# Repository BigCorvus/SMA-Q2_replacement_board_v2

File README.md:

# SMA-Q2_replacement_board_v2

nRF5840-based replacement board for the SMA-Q2 smartwatch. Uses the MDBT50Q-1MV2 (and similar) module. Based on the Adafruit Feather nRF52840. Has to be fabricated on 0,8mm FR4 material. Main changes are: no external RTC, all mosfets in SOT-323 package (at least in v2.2), optional barometer and power latching circuit, everything controlled by the nRF52840.

2 versions have been created: v2.2 without MS5611 barometer, but with a simple power latching circuit. v2.1.1 does not have a power latching circuit, but has a footprint for a MS5611 barometer. Both versions use both interrupts of the accelerometer.  
During testing and everyday use RF performance turned out to be poor. The reason is the ceramic antenna which is shielded by the close proximity of the lipo battery. This problem was quite easy to solve in retrospective. I just desoldered the chip antenna with 2 soldering irons and connected a simple 30AWG wire which I shortened until reception started to get worse. Ended up with about 20mm of wire bent around the top left corner of the device where least interfering metal is located. Quite surprising that the antenna is quite a bit shorter than one would expect for 2.4GHz (lambda/4 = ~31mm). Let me tell you, at 5dbm TX power the wireless range and link reliability is now really good! FCC compliance is now goneski of course.  
This got me motivated to create a 3rd version of the board using the bare chip instead of an integrated module. It makes use of the inbuilt antenna which is also surprisingly short (about 20mm). The feedline was designed to be about 50 ohm (although it probably doesn't have to be, in the original version it's about 65 ohm at 0,7mm trace width and 0.8mm FR4 substrate). This version 2.3 has the barometer, which has proven to be very accurate and useful, the power latching circuit and even a fuel gauge which can measure the supply current (albeit in 1mA steps).  
Another feature that proved to be very useful if you like to wear a dev platform on your wrist is a normally closed reed switch in series with the battery so you can power cycle the device if bricked with a magnet (the charging cable f.e.) or just keep the battey disconnected by attaching a magnet to it if the device is not in use and has to be stored for longer periods of time. The pads on the bottom of the board are there to keep the reed switch in place. The battery therefore connects to the leftmost contact (one arm of the reed switch) and GND. I used the smallest SPDT (3 pins) reed switch I could find. Its glass body is 15mm long. Just trim the unused leg and bend the other two in shape carefully making sure the delicate glass body stays intact.   

Note: 2.3 has not been tested yet. The Feather bootloader should still work, the pinout for the button, I2C, SPI, QSPI and UART is still the same.

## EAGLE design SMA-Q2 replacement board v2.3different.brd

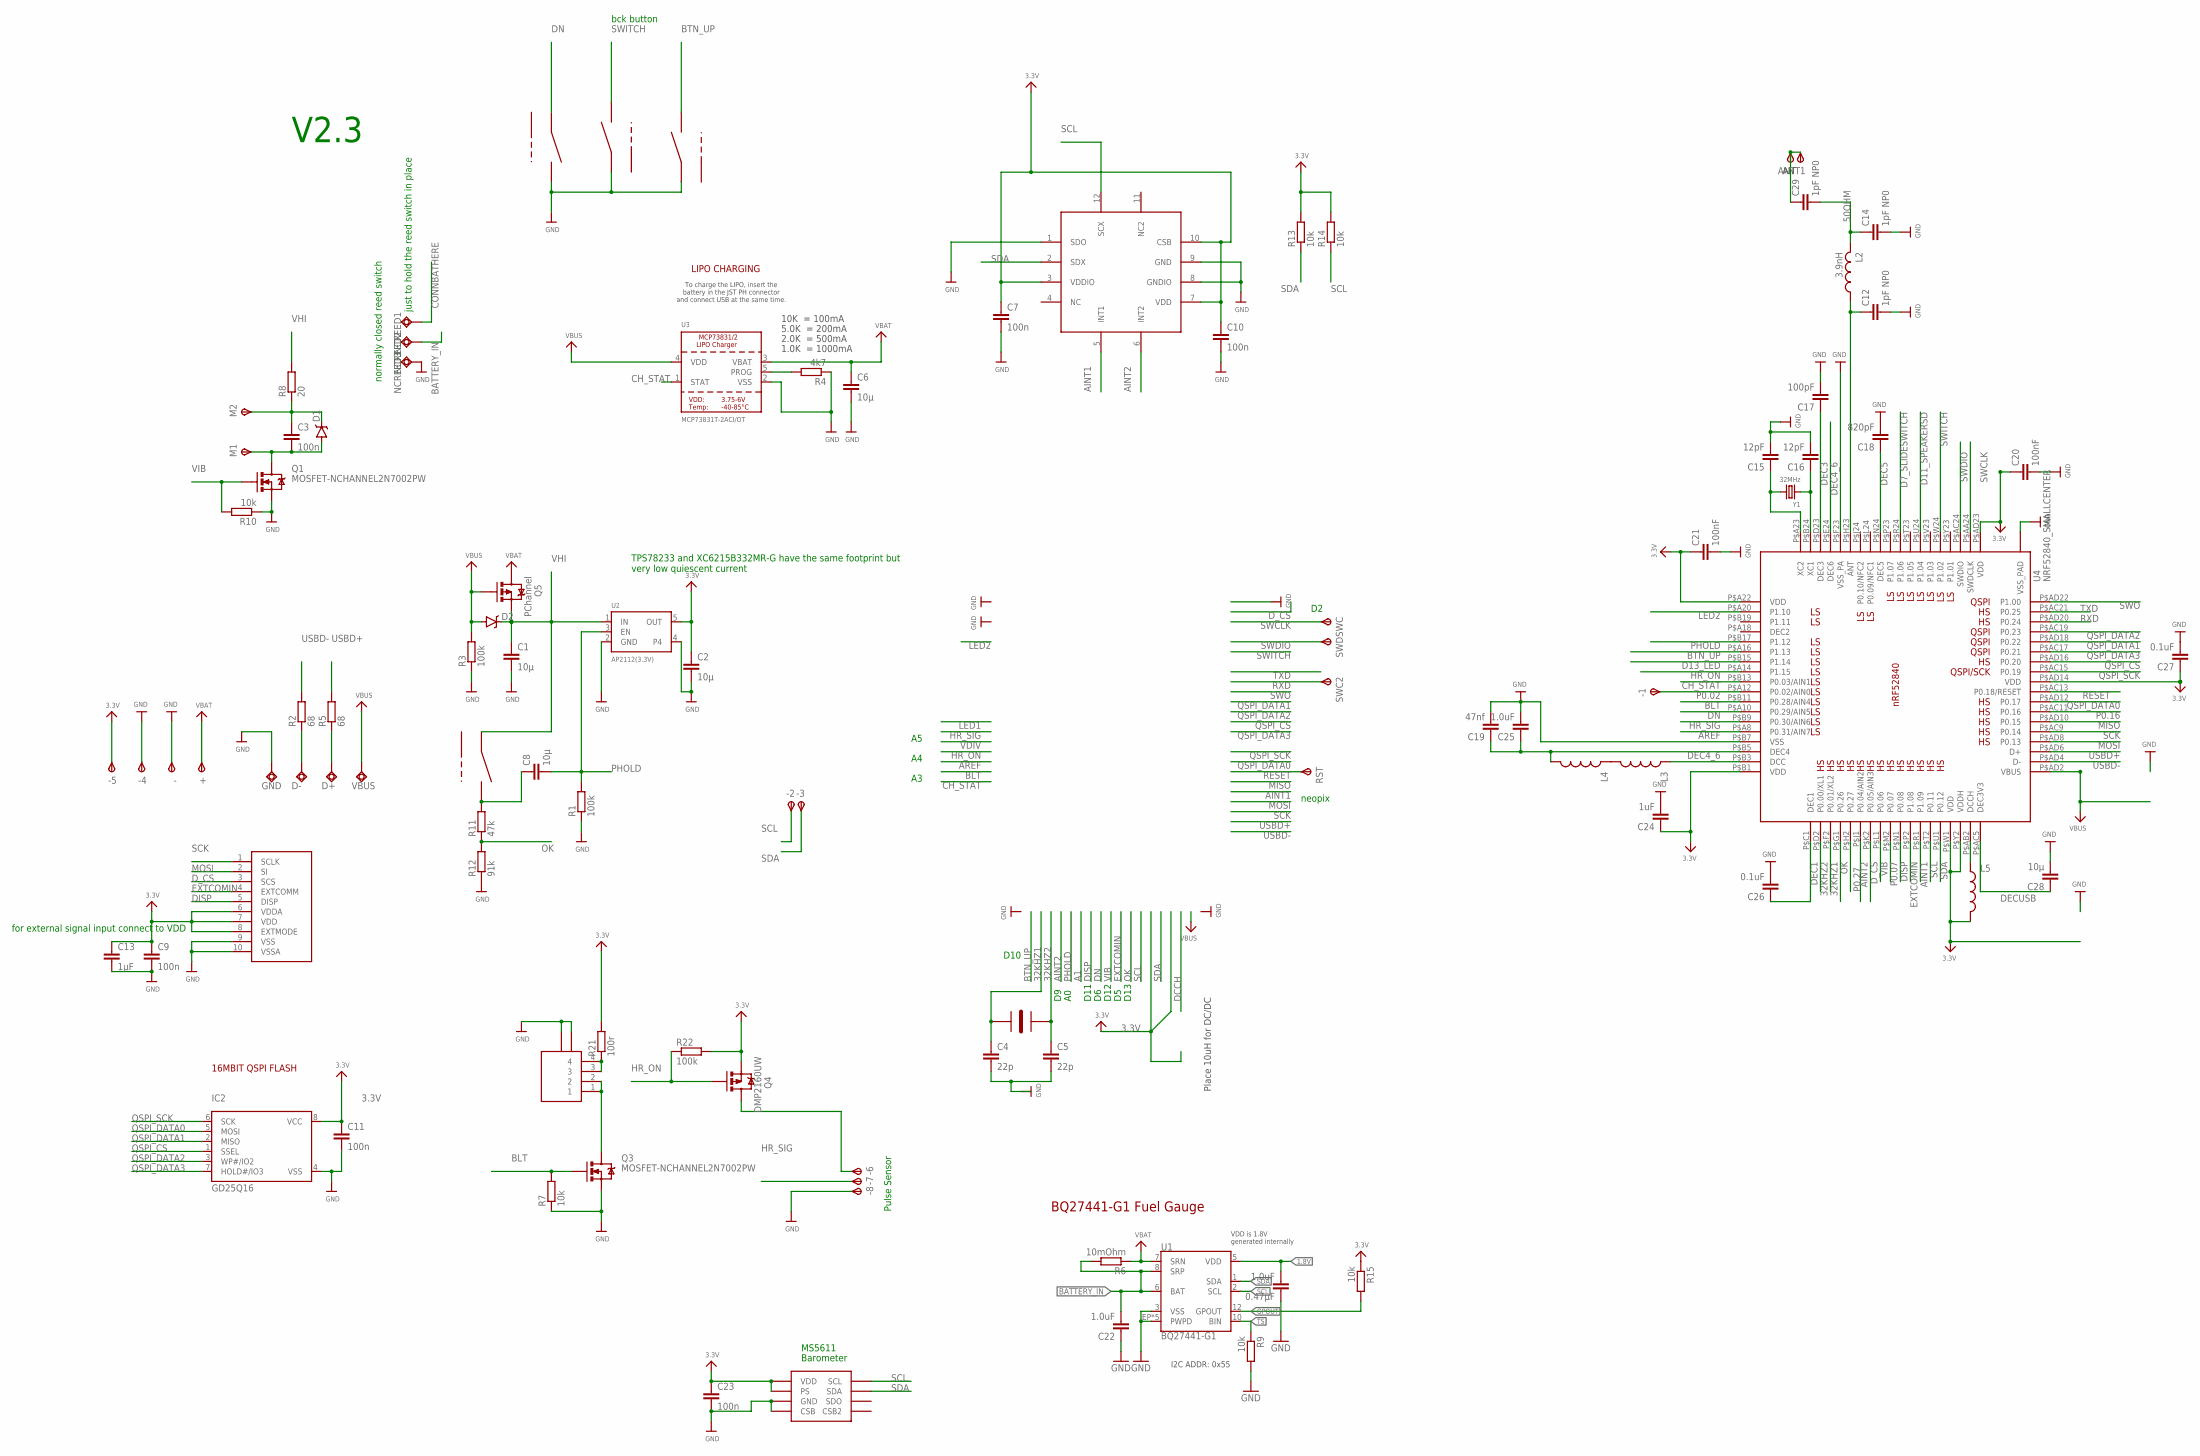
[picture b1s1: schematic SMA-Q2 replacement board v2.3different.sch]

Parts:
0.47µF: 1.0uF; RESC0603_N
+: TPSTP09R; TP09R
-, -1, -2, -3, -4, -5, -6, -7, -8: TPSTP09R; TP09R
ANT, ANT1: TPSTP19SQ; TP19SQ
C1, C2, C6, C8, C28: 10µ; C0603
C3, C7, C9, C10, C11, C23: 100n; C0402
C4, C5: 22p; C0402
C12, C14, C29: 1pF NP0; RESC0402_N
C13: 1µF; C0402
C15, C16: 12pF; RESC0402_N
C17: 100pF; RESC0402_N
C18: 820pF; RESC0402_N
C19: 47nf; RESC0603_N
C20, C21: 100nF; RESC0402_N
C22, C25: 1.0uF; RESC0603_N
C24: 1uF; RESC0603_N
C26: 0.1uF; RESC0603_N
C27: 0.1uF; RESC0402_N
D1, D2: BAT20J; SOD-323
D+: TPSQTP20R; TP20R
D-: TPSQTP20R; TP20R
DWN, DWN1, DWN2, DWN3: LS12T2
GND: TPSQTP20R; TP20R
IC2: GD25Q16; USON8
L2: 3.9nH; RESC0402_N
L3, L5: INDUCTOR30OHM,1.8A; 0603
L4: INDUCTOR0402; C0402
M1, M2: TPSTP09R; TP09R
NCREED1, NCREED2, NCREED3: TPSQTP20R; TP20R
Q1, Q3: MOSFET-NCHANNEL2N7002PW; SOT323
Q4: DMP2160UW; SOT323
Q5: PChannel; SOT323
R1, R3, R22: 100k; R0402
R2, R5: 68; R0402
R4: 4k7; R0402
R6: 10mOhm; R0402
R7, R9, R10, R13, R14, R15: 10k; R0402
R8: 20; R0402
R11: 47k; R0402
R12: 91k; R0402
R21: 100r; R0402
RST: TPSTP09R; TP09R
SWC, SWC2: TPSTP09R; TP09R
SWD: TPSTP09R; TP09R
U1: BQ27441-G1; PDSO-N12
U2: AP2112(3.3V); SOT23-5
U3: MCP73831T-2ACI/OT; SOT23-5
U4: NRF52840_SMALLCENTER; AQFN50P700X800X85_HS-74N_SMALLCENTER
U$2: SHARP_MEM_DISP; Y5BW
U$6: Y5B-4PIN
U$7: BMA400
U$45: MC5611; MS5611
U$81: ECX-1210
VBUS: TPSQTP20R; TP20R
Y1: 32MHz; CRYSTAL_2.5X2

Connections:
1.8V: 0.47µF.2, U1.5 (VDD)
3.3V: -5.TP, C2.1, C7.1, C9.1, C10.1, C11.1, C13.1, C20.1, C21.1, C23.1, C24.1, C27.1, IC2.8 (VCC), L5.2, Q4.2 (S), R13.2, R14.2, R15.1, R21.2, R22.2, U2.5 (OUT), U4.P$A22 (VDD), U4.P$AD14 (VDD), U4.P$AD23 (VDD), U4.P$B1 (VDD), U4.P$W1 (VDD), U4.P$Y2 (VDDH), U$2.6 (VDDA), U$2.7 (VDD), U$2.8 (EXTMODE), U$7.3 (VDDIO), U$7.7 (VDD), U$7.10 (CSB), U$45.PS, U$45.VDD
32KHZ1: C4.1, U4.P$F2 (P0.01/XL2), U$81.P$1
32KHZ2: C5.1, U4.P$D2 (P0.00/XL1), U$81.P$2
50OHM: C14.1, C29.2, L2.2
AINT1: U4.P$R1 (P1.09), U$7.5 (INT1)
AINT2: U4.P$J1 (P0.04/AIN2), U$7.6 (INT2)
AREF: U4.P$A8 (P0.31/AIN7)
BATTERY_IN: C22.2, NCREED2.TP, R6.2, U1.6 (BAT), U1.8 (SRP)
BLT: Q3.1 (G), R7.2, U4.P$B11 (P0.28/AIN4)
BTN_UP: DWN2.1, U4.P$A16 (P1.13)
CH_STAT: U3.1 (STAT), U4.P$B13 (P0.03/AIN1)
CONNBATHERE: NCREED1.TP
D7_SLIDESWITCH: U4.P$R24 (P1.06)
D11_SPEAKERSD: U4.P$U24 (P1.04)
D13_LED: U4.P$B15 (P1.14)
DEC1: C26.1, U4.P$C1 (DEC1)
DEC3: C17.1, U4.P$D23 (DEC3)
DEC4_6: C19.1, C25.1, L4.2, U4.P$B5 (DEC4), U4.P$E24 (DEC6)
DEC5: C18.1, U4.P$N24 (DEC5)
DECUSB: C28.1, U4.P$AC5 (DEC3V3)
DISP: U4.P$N1 (P0.08), U$2.5 (DISP)
DN: DWN.2, U4.P$A10 (P0.29/AIN5)
D_CS: U4.P$K2 (P0.05/AIN3), U$2.3 (SCS)
EXTCOMIN: U4.P$P2 (P1.08), U$2.4 (EXTCOMM)
GND: 0.47µF.1, -.TP, -4.TP, -8.TP, C1.2, C2.2, C4.2, C5.2, C6.2, C7.2, C9.2, C10.2, C11.2, C12.2, C13.2, C14.2, C15.2, C16.2, C17.2, C18.2, C19.2, C20.2, C21.2, C22.1, C23.2, C24.2, C25.2, C26.2, C27.2, C28.2, DWN.1, DWN1.2, DWN2.2, GND.TP, IC2.4 (VSS), NCREED3.TP, Q1.2 (S), Q3.2 (S), R1.1, R3.1, R4.1, R7.1, R9.2, R10.1, R12.1, U1.3 (VSS), U1.EP (PWPD), U1.EP1 (PWPD), U1.EP2 (PWPD), U1.EP3 (PWPD), U1.EP4 (PWPD), U2.2 (GND), U2.4, U3.2 (VSS), U4.P$B7 (VSS), U4.P$F23 (VSS_PA), U4.THERMPAD (VSS_PAD), U$2.9 (VSS), U$2.10 (VSSA), U$6.H1, U$6.H2, U$7.1 (SDO), U$7.8 (GNDIO), U$7.9 (GND), U$45.CSB, U$45.GND
GPOUT: R15.2, U1.12 (GPOUT)
HR_ON: Q4.1 (G), R22.1, U4.P$A14 (P1.15)
HR_SIG: -7.TP, U4.P$B9 (P0.30/AIN6)
LED2: U4.P$A20 (P1.10)
MISO: U4.P$AD10 (P0.15)
MOSI: U4.P$AD8 (P0.13), U$2.2 (SI)
unnamed: Q3.3 (D), U$6.1, U$6.2
unnamed: C8.1, DWN3.1, R11.2
unnamed: D-.TP, R2.1
unnamed: D+.TP, R5.1
unnamed: C12.1, L2.1, U4.P$H23 (ANT)
unnamed: L3.2, L4.1
unnamed: L3.1, U4.P$B3 (DCC)
unnamed: L5.1, U4.P$AB2 (DCCH)
unnamed: R21.1, U$6.3, U$6.4
unnamed: -6.TP, Q4.3 (D)
unnamed: R4.2, U3.5 (PROG)
unnamed: C3.2, D1.A, M1.TP, Q1.3 (D)
unnamed: C3.1, D1.C, M2.TP, R8.1
unnamed: C15.1, U4.P$A23 (XC2), Y1.3 (2)
unnamed: C16.1, U4.P$B24 (XC1), Y1.1
OK: R11.1, R12.2, U4.P$G1 (P0.26)
P0.02: -1.TP, U4.P$A12 (P0.02/AIN0)
P0.07: U4.P$M2 (P0.07)
P0.16: U4.P$AC11 (P0.16)
P0.27: U4.P$H2 (P0.27)
PHOLD: C8.2, R1.2, U2.3 (EN), U4.P$B17 (P1.12)
QSPI_CS: IC2.1 (SSEL), U4.P$AD16 (P0.20)
QSPI_DATA0: IC2.5 (MOSI), U4.P$AD12 (P0.17)
QSPI_DATA1: IC2.2 (MISO), U4.P$AD18 (P0.22)
QSPI_DATA2: IC2.3 (WP#/IO2), U4.P$AC19 (P0.23)
QSPI_DATA3: IC2.7 (HOLD#/IO3), U4.P$AC17 (P0.21)
QSPI_SCK: IC2.6 (SCK), U4.P$AC15 (P0.19)
RESET: RST.TP, U4.P$AC13 (P0.18/RESET)
RF: ANT.TP, ANT1.TP, C29.1
RXD: SWC2.TP, U4.P$AD20 (P0.24)
SCK: U4.P$AC9 (P0.14), U$2.1 (SCLK)
SCL: -2.TP, R14.1, U1.2 (SCL), U4.P$T2 (P0.11), U$7.12 (SCX), U$45.SCL
SDA: -3.TP, R13.1, U1.1 (SDA), U4.P$U1 (P0.12), U$7.2 (SDX), U$45.SDA
SWCLK: SWC.TP, U4.P$AA24 (SWDCLK)
SWDIO: SWD.TP, U4.P$AC24 (SWDIO)
SWITCH: DWN1.1, U4.P$W24 (P1.02)
SWO: U4.P$AD22 (P1.00)
TS: R9.1, U1.10 (BIN)
TXD: U4.P$AC21 (P0.25)
USBD+: R5.2, U4.P$AD6 (D+)
USBD-: R2.2, U4.P$AD4 (D-)
VBAT: +.TP, C6.1, Q5.3 (D), R6.1, U1.7 (SRN), U3.3 (VBAT)
VBUS: D2.A, Q5.1 (G), R3.2, U3.4 (VDD), U4.P$AD2 (VBUS), VBUS.TP
VHI: C1.1, D2.C, DWN3.2, Q5.2 (S), R8.2, U2.1 (IN)
VIB: Q1.1 (G), R10.2, U4.P$L1 (P0.06)

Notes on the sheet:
Place 10uH for DC/DC
10K = 100mA
5.0K = 200mA
2.0K = 500mA
1.0K = 1000mA
LIPO CHARGING
To charge the LIPO, insert the battery in the JST PH connector and connect USB at the same time.
TPS78233 and XC6215B332MR-G have the same footprint but very low quiescent current
16MBIT QSPI FLASH
for external signal input connect to VDD
D10
D12
neopix
D13
D11
bck button
V2.3
normally closed reed switch
Pulse Sensor
MS5611
Barometer
BQ27441-G1 Fuel Gauge
VDD is 1.8V generated internally
I2C ADDR: 0x55
just to hold the reed switch in place

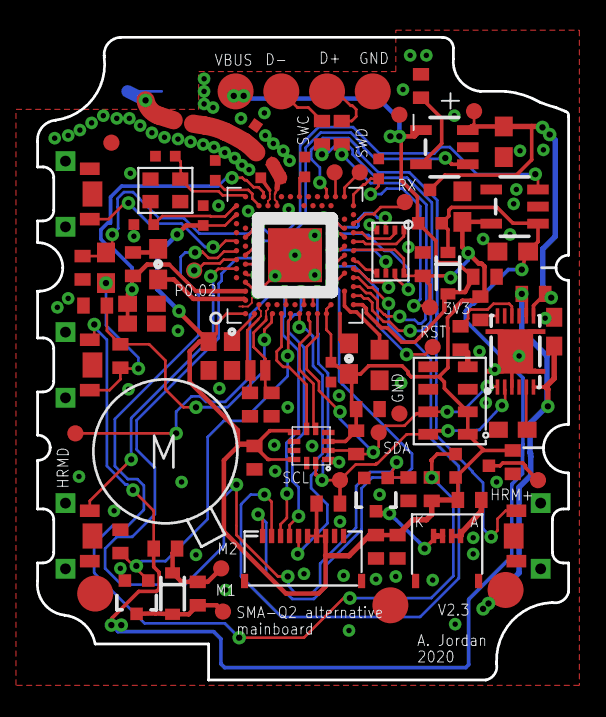
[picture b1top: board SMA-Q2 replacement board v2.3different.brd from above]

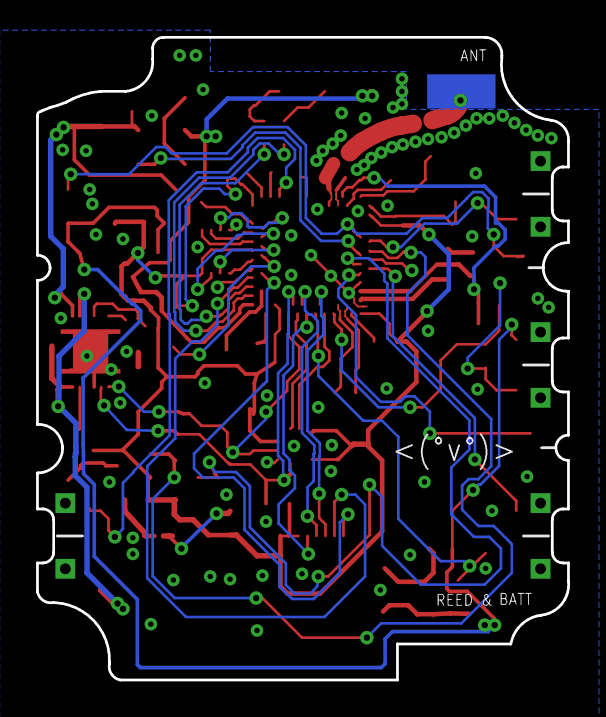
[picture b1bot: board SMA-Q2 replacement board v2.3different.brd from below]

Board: 2 copper layers, 29.5 x 35.7 mm, 97 parts (2 on the bottom side), 65 nets.

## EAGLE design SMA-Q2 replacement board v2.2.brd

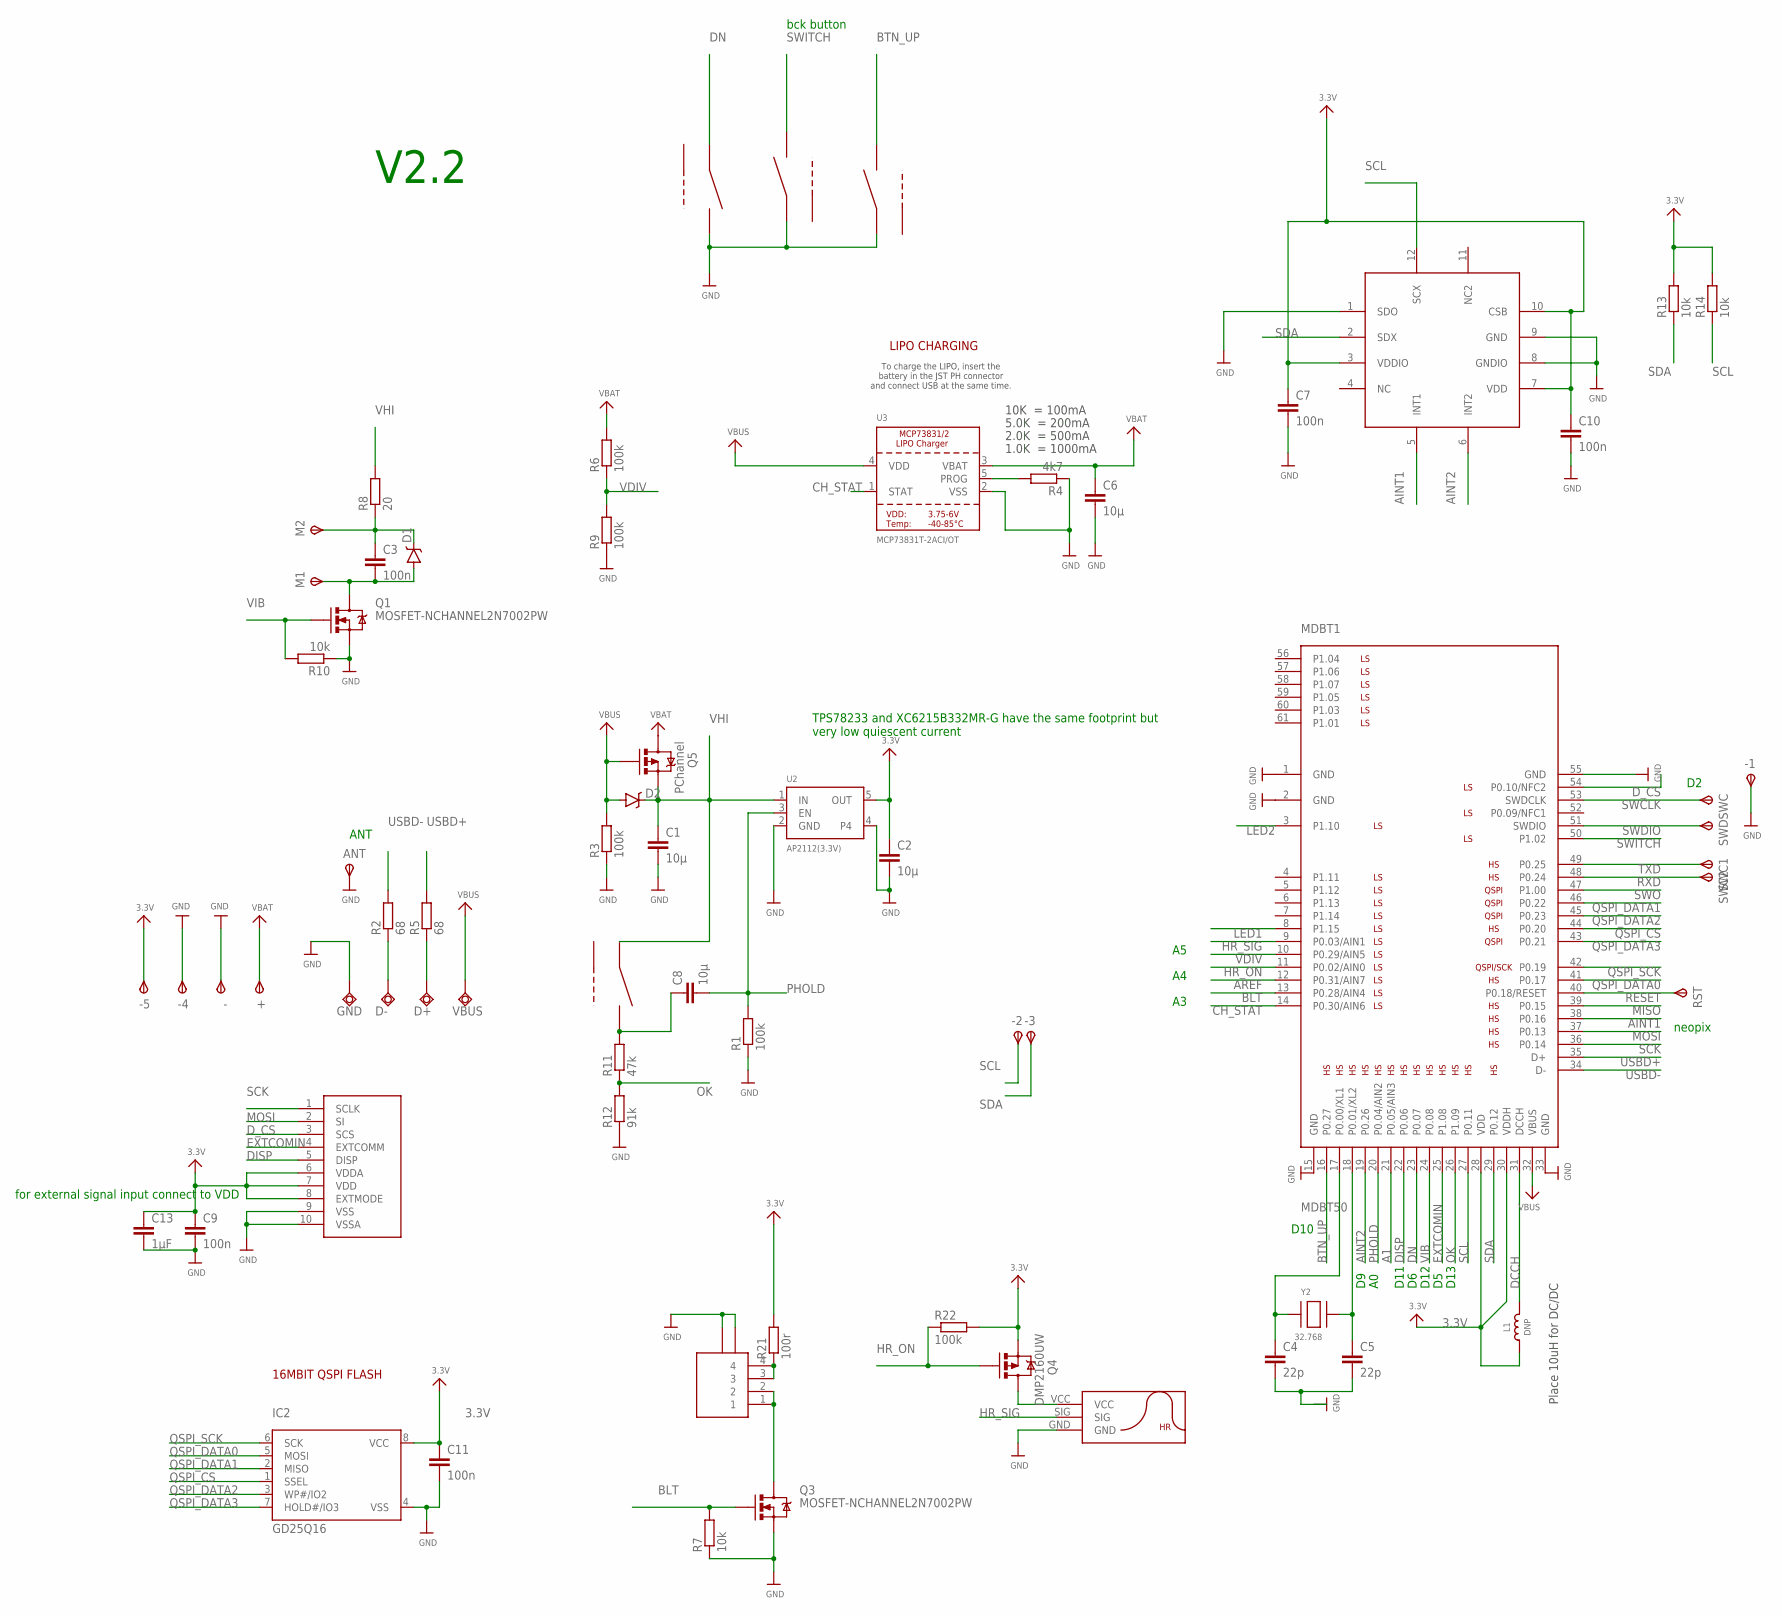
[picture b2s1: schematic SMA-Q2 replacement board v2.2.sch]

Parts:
+: TPSTP09R; TP09R
-, -1, -2, -3, -4, -5: TPSTP09R; TP09R
ANT: TPSTP19SQ; TP19SQ
C1, C2, C6, C8: 10µ; C0603
C3, C7, C9, C10, C11: 100n; C0402
C4, C5: 22p; C0402
C13: 1µF; C0402
D1, D2: BAT20J; SOD-323
D+: TPSQTP20R; TP20R
D-: TPSQTP20R; TP20R
DWN, DWN1, DWN2, DWN3: LS12T2
GND: TPSQTP20R; TP20R
IC2: GD25Q16; USON8
L1: DNP; _0805MP
M1, M2: TPSTP09R; TP09R
MDBT1: MDBT50
Q1, Q3: MOSFET-NCHANNEL2N7002PW; SOT323
Q4: DMP2160UW; SOT323
Q5: PChannel; SOT323
R1, R3, R6, R9, R22: 100k; R0402
R2, R5: 68; R0402
R4: 4k7; R0402
R7, R10, R13, R14: 10k; R0402
R8: 20; R0402
R11: 47k; R0402
R12: 91k; R0402
R21: 100r; R0402
RST: TPSTP09R; TP09R
SWC, SWC1, SWC2: TPSTP09R; TP09R
SWD: TPSTP09R; TP09R
U2: AP2112(3.3V); SOT23-5
U3: MCP73831T-2ACI/OT; SOT23-5
U$2: SHARP_MEM_DISP; Y5BW
U$6: Y5B-4PIN
U$7: BMA400
U$45: HR_PADS
VBUS: TPSQTP20R; TP20R
Y2: 32.768; XTAL3215

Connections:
3.3V: -5.TP, C2.1, C7.1, C9.1, C10.1, C11.1, C13.1, IC2.8 (VCC), L1.1, MDBT1.28 (VDD), MDBT1.30 (VDDH), Q4.2 (S), R13.2, R14.2, R21.2, R22.2, U2.5 (OUT), U$2.6 (VDDA), U$2.7 (VDD), U$2.8 (EXTMODE), U$7.3 (VDDIO), U$7.7 (VDD), U$7.10 (CSB)
A1: MDBT1.21 (P0.05/AIN3)
AINT1: MDBT1.38 (P0.16), U$7.5 (INT1)
AINT2: MDBT1.19 (P0.26), U$7.6 (INT2)
AREF: MDBT1.12 (P0.31/AIN7)
BLT: MDBT1.13 (P0.28/AIN4), Q3.1 (G), R7.2
BTN_UP: DWN2.1, MDBT1.16 (P0.27)
CH_STAT: MDBT1.14 (P0.30/AIN6), U3.1 (STAT)
DCCH: L1.2, MDBT1.31 (DCCH)
DISP: MDBT1.22 (P0.06), U$2.5 (DISP)
DN: DWN.2, MDBT1.23 (P0.07)
D_CS: MDBT1.54 (P0.10/NFC2), U$2.3 (SCS)
EXTCOMIN: MDBT1.25 (P1.08), U$2.4 (EXTCOMM)
GND: -.TP, -1.TP, -4.TP, ANT.TP, C1.2, C2.2, C4.2, C5.2, C6.2, C7.2, C9.2, C10.2, C11.2, C13.2, DWN.1, DWN1.2, DWN2.2, GND.TP, IC2.4 (VSS), MDBT1.1 (GND), MDBT1.2 (GND), MDBT1.15 (GND), MDBT1.33 (GND), MDBT1.55 (GND), Q1.2 (S), Q3.2 (S), R1.1, R3.1, R4.1, R7.1, R9.1, R10.1, R12.1, U2.2 (GND), U2.4, U3.2 (VSS), U$2.9 (VSS), U$2.10 (VSSA), U$6.H1, U$6.H2, U$7.1 (SDO), U$7.8 (GNDIO), U$7.9 (GND), U$45.GND
HR_ON: MDBT1.11 (P0.02/AIN0), Q4.1 (G), R22.1
HR_SIG: MDBT1.9 (P0.03/AIN1), U$45.SIG
LED1: MDBT1.8 (P1.15)
LED2: MDBT1.3 (P1.10)
MISO: MDBT1.39 (P0.15)
MOSI: MDBT1.37 (P0.13), U$2.2 (SI)
unnamed: Q3.3 (D), U$6.1, U$6.2
unnamed: C8.1, DWN3.1, R11.2
unnamed: D-.TP, R2.1
unnamed: D+.TP, R5.1
unnamed: C4.1, MDBT1.17 (P0.00/XL1), Y2.P$1
unnamed: C5.1, MDBT1.18 (P0.01/XL2), Y2.P$2
unnamed: R21.1, U$6.3, U$6.4
unnamed: R4.2, U3.5 (PROG)
unnamed: C3.2, D1.A, M1.TP, Q1.3 (D)
unnamed: C3.1, D1.C, M2.TP, R8.1
unnamed: Q4.3 (D), U$45.VCC
OK: MDBT1.26 (P1.09), R11.1, R12.2
PHOLD: C8.2, MDBT1.20 (P0.04/AIN2), R1.2, U2.3 (EN)
QSPI_CS: IC2.1 (SSEL), MDBT1.44 (P0.20)
QSPI_DATA0: IC2.5 (MOSI), MDBT1.41 (P0.17)
QSPI_DATA1: IC2.2 (MISO), MDBT1.46 (P0.22)
QSPI_DATA2: IC2.3 (WP#/IO2), MDBT1.45 (P0.23)
QSPI_DATA3: IC2.7 (HOLD#/IO3), MDBT1.43 (P0.21)
QSPI_SCK: IC2.6 (SCK), MDBT1.42 (P0.19)
RESET: MDBT1.40 (P0.18/RESET), RST.TP
RXD: MDBT1.48 (P0.24), SWC2.TP
SCK: MDBT1.36 (P0.14), U$2.1 (SCLK)
SCL: -2.TP, MDBT1.27 (P0.11), R14.1, U$7.12 (SCX)
SDA: -3.TP, MDBT1.29 (P0.12), R13.1, U$7.2 (SDX)
SWCLK: MDBT1.53 (SWDCLK), SWC.TP
SWDIO: MDBT1.51 (SWDIO), SWD.TP
SWITCH: DWN1.1, MDBT1.50 (P1.02)
SWO: MDBT1.47 (P1.00)
TXD: MDBT1.49 (P0.25), SWC1.TP
USBD+: MDBT1.35 (D+), R5.2
USBD-: MDBT1.34 (D-), R2.2
VBAT: +.TP, C6.1, Q5.3 (D), R6.2, U3.3 (VBAT)
VBUS: D2.A, MDBT1.32 (VBUS), Q5.1 (G), R3.2, U3.4 (VDD), VBUS.TP
VDIV: MDBT1.10 (P0.29/AIN5), R6.1, R9.2
VHI: C1.1, D2.C, DWN3.2, Q5.2 (S), R8.2, U2.1 (IN)
VIB: MDBT1.24 (P0.08), Q1.1 (G), R10.2

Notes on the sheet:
Place 10uH for DC/DC
10K = 100mA
5.0K = 200mA
2.0K = 500mA
1.0K = 1000mA
LIPO CHARGING
To charge the LIPO, insert the battery in the JST PH connector and connect USB at the same time.
ANT
TPS78233 and XC6215B332MR-G have the same footprint but very low quiescent current
16MBIT QSPI FLASH
for external signal input connect to VDD
D10
D12
neopix
D13
D11
bck button
V2.2

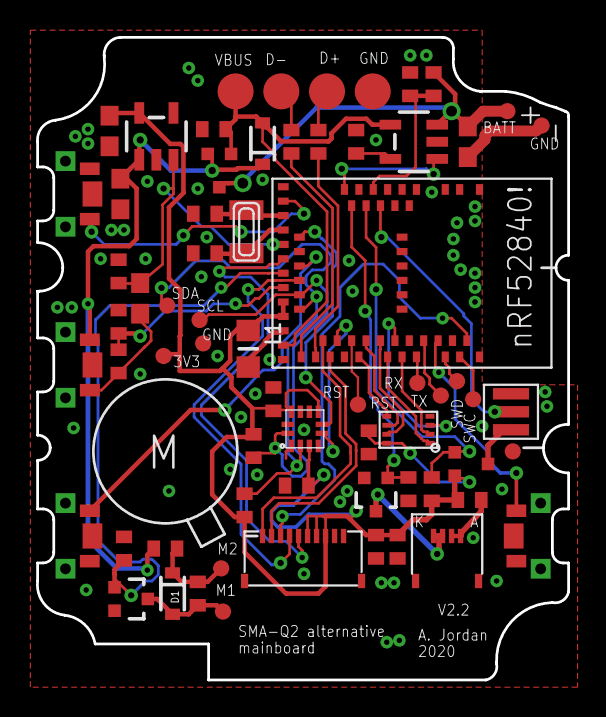
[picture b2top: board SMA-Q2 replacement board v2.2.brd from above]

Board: 2 copper layers, 29.5 x 35.7 mm, 67 parts (1 on the bottom side), 50 nets.

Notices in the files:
parts and their libraries:
microbuilder: This work is placed in the public domain, and may be freely used for commercial and non-commercial work with the following conditions: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
SparkFun-DiscreteSemi: Licensing: Creative Commons ShareAlike 4.0 International - https://creativecommons.org/licenses/by-sa/4.0
